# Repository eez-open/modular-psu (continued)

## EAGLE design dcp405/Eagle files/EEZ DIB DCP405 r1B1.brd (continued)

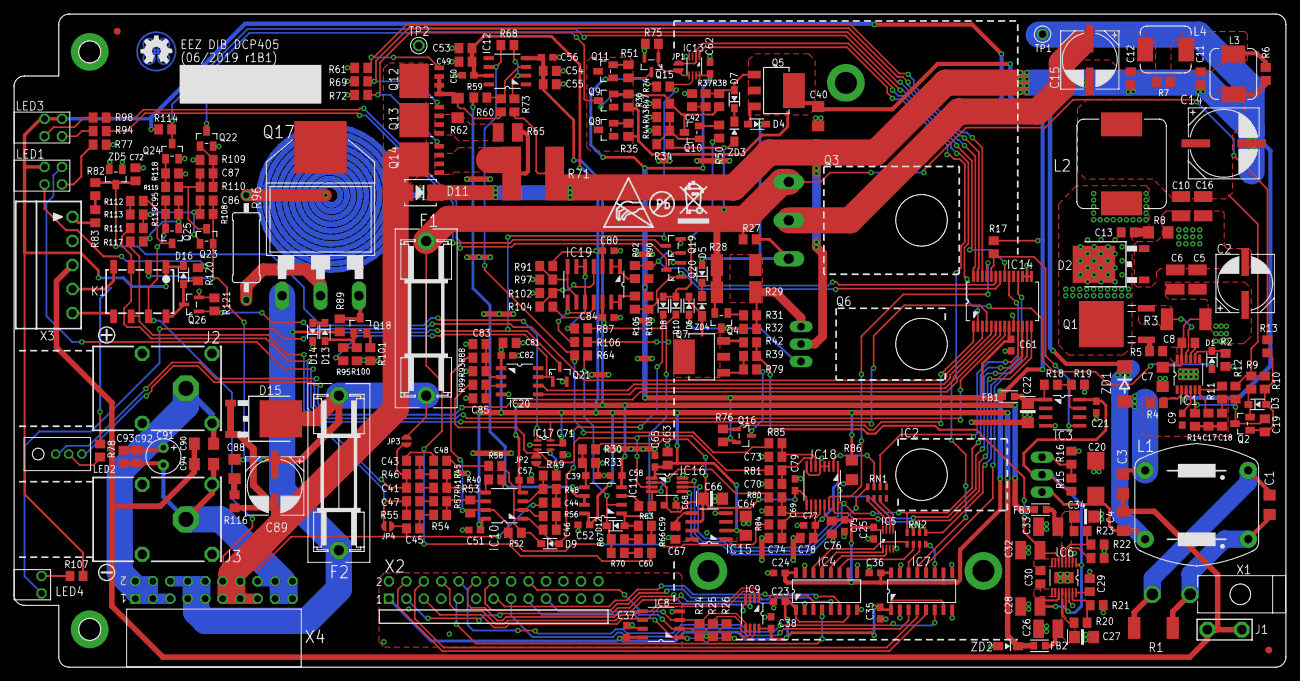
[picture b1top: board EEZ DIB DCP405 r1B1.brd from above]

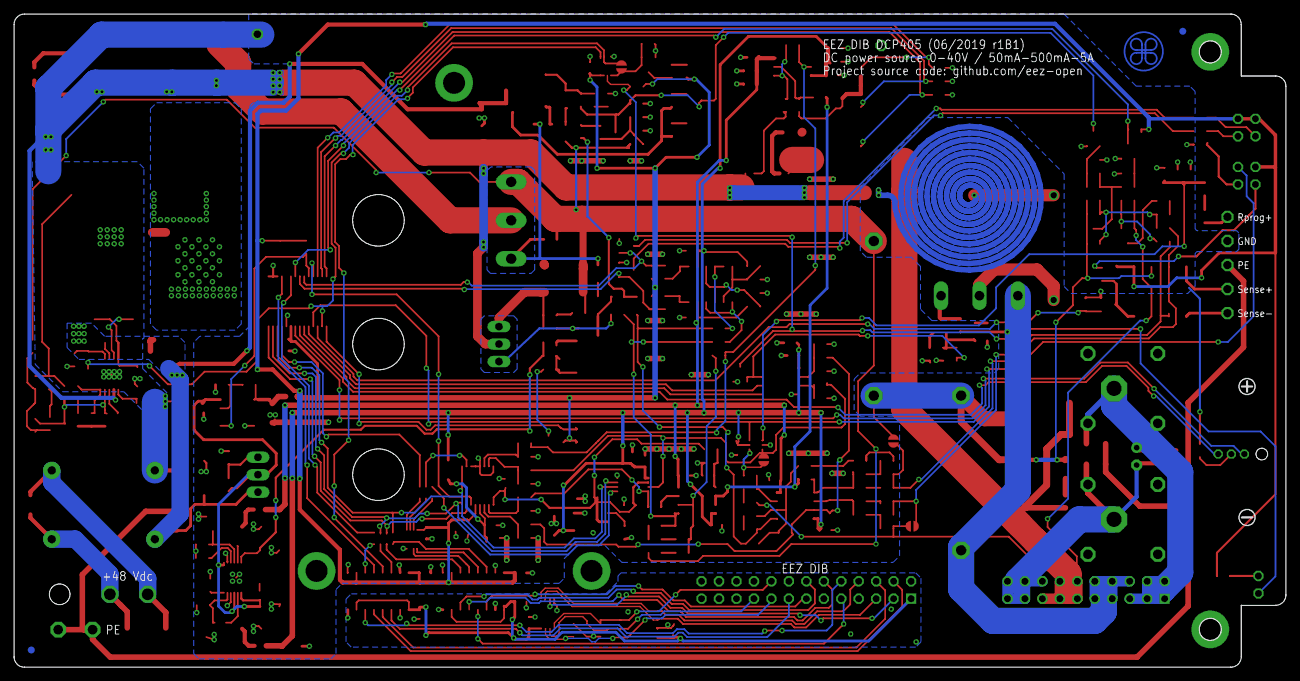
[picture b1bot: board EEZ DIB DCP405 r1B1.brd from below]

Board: 2 copper layers, 185.0 x 95.0 mm, 323 parts (3 on the bottom side), 200 nets.

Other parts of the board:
EEZ_SIGNATURE: SIGNATURESMALL; SIGNATURE_5MM
U$1: RECYCLE_BIN1/8
U$6: ESD_SYMBOL
U$7: PB_SMALL

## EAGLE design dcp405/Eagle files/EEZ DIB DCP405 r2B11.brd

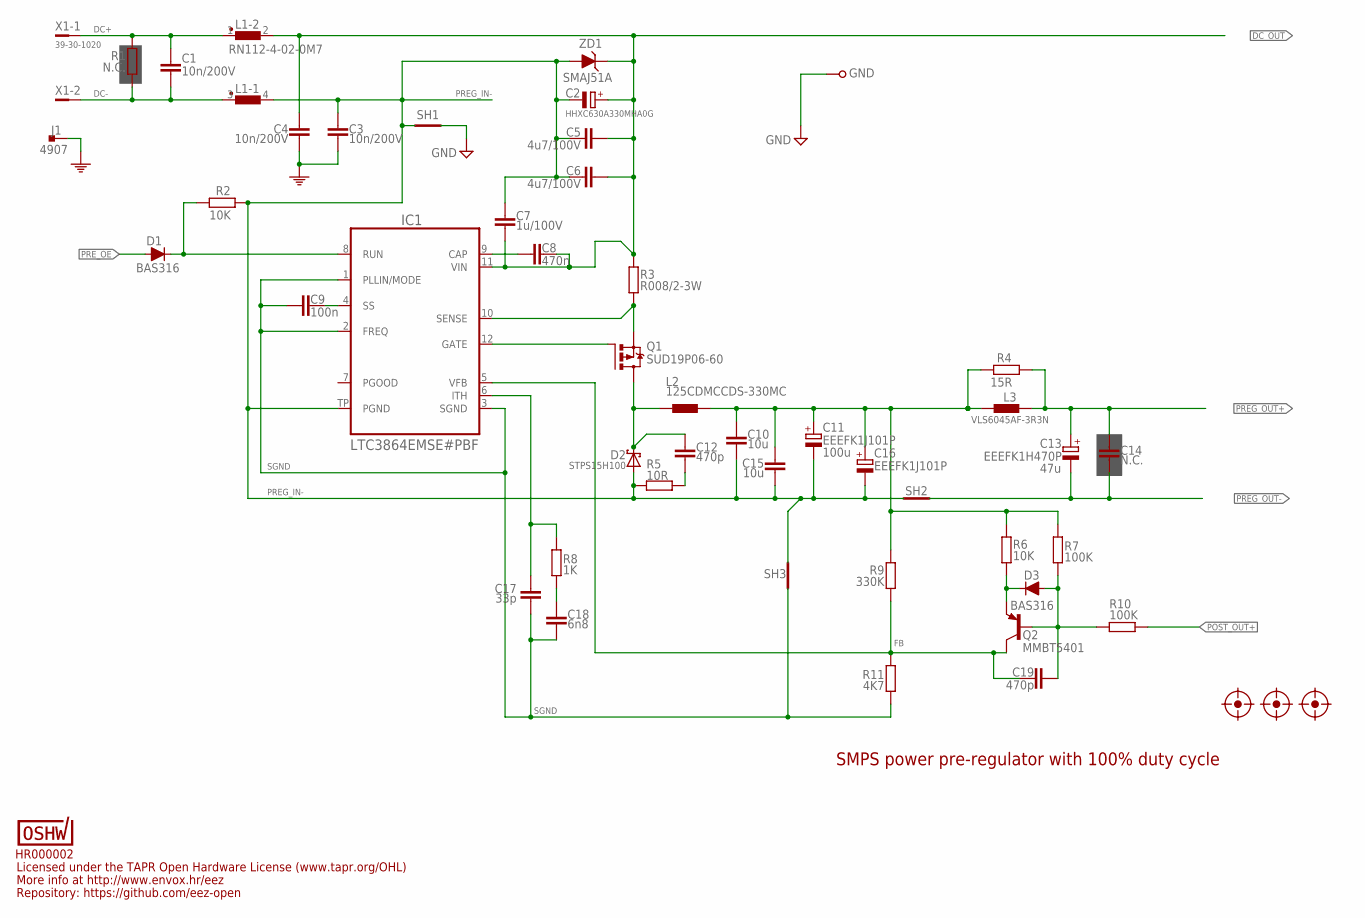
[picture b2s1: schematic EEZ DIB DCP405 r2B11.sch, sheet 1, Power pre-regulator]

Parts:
C1, C3, C4: 10n/200V; C1206
C2: HHXC630A330MHA0G; CAPAE830X1050N
C5, C6: 4u7/100V; C1210
C7: 1u/100V; C1206
C8: 470n; C0805
C9: 100n; C0603
C10, C15: 10u; C1210
C11, C16: EEEFK1J101P; CAPAE1030X1050N
C12, C19: 470p; C0805
C13: EEEFK1H470P; CAPAE830X1050N
C14: N.C.; C0805
C17: 33p; C0805
C18: 6n8; C0805
D1, D3: BAS316; SOD323-R
D2: STPS15H100; TO252-L
FM1, FM2, FM3: FIDUCIAL_2; FIDUCIAL_DUAL
GND: PCB_TEST_TABSHIELD; PCB_SHIELD_TAB
IC1: LTC3864EMSE#PBF; LTC_05-08-1666
J1: 4907; PCB_TAB-4907
L1: RN112-4-02-0M7; RN112
L2: 125CDMCCDS-330MC; 125CDMCC/DS
L3: VLS6045AF-3R3N; COILCRAFT_HPI0630
OSHWA: HR000002; CERT-SMALL-SILK
Q1: SUD19P06-60; TO229P990X239-3N
Q2: MMBT5401; SOT23-BEC
R1: N.C.; R2512
R2, R6: 10K; R0805
R3: R008/2-3W; R2512
R4: 15R; R2010
R5: 10R; R1206
R7, R10: 100K; R0805
R8: 1K; R0805
R9: 330K; R0805
R11: 4K7; R0805
SH1: SHORTNOHOLE; SHORT_NOHOLE
SH2: Pgnd to Pout- short; SHORT_NOHOLE
SH3: Sgnd to Pgnd short; SHORT_NOHOLE
X1: 39-30-1020; MINIFIT_39301020
ZD1: SMAJ51A; DO214AA

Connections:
DC+: C1.2, L1.1, R1.2, X1.1
DC-: C1.1, L1.3 (1), R1.1, X1.2
DC_OUT: C2.+, C4.2, C5.1, C6.1, C7.1, C8.2, IC1.11 (VIN), L1.2, R3.1, ZD1.C; also elsewhere on the board
FB: C19.1, IC1.5 (VFB), Q2.C, R9.2, R11.1
GND: GND.1, SH1.2 (GND_B); also elsewhere on the board
L_OUT: C10.1, C11.+, C15.1, C16.+, L2.2, L3.1, R4.1, R6.1, R7.1, R9.1
unnamed: D3.C, Q2.E, R6.2
unnamed: C18.1, R8.1
unnamed: D1.C, IC1.8 (RUN), R2.2
unnamed: C17.1, IC1.6 (ITH), R8.2
unnamed: C8.1, IC1.9 (CAP)
unnamed: C9.2, IC1.4 (SS)
unnamed: IC1.12 (GATE), Q1.1 (G)
unnamed: C12.2, R5.2
unnamed: C19.2, D3.A, Q2.B, R7.2, R10.1
PE: C3.2, C4.1, J1.1, J1.2; also elsewhere on the board
POST_OUT+: R10.2; also elsewhere on the board
PREG_IN-: C2.-, C3.1, C5.2, C6.2, C7.2, C10.2, C11.-, C15.2, C16.-, D2.1 (A), D2.2 (A), IC1.TP (PGND), L1.4 (2), R2.1, R5.1, SH1.1 (GND_A), SH2.2 (GND_B), SH3.2 (GND_B), ZD1.A
PREG_OUT+: C13.+, C14.1, L3.2, R4.2; also elsewhere on the board
PREG_OUT-: C13.-, C14.2, SH2.1 (GND_A); also elsewhere on the board
PRE_OE: D1.A; also elsewhere on the board
SENSE: IC1.10 (SENSE), Q1.3 (S), R3.2
SGND: C9.1, C17.2, C18.2, IC1.1 (PLLIN/MODE), IC1.2 (FREQ), IC1.3 (SGND), R11.2, SH3.1 (GND_A)
SW: C12.1, D2.3 (C), L2.1, Q1.2 (D)

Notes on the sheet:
47u
Licensed under the TAPR Open Hardware License (www.tapr.org/OHL)
Repository: https://github.com/eez-open
More info at http://www.envox.hr/eez
SMPS power pre-regulator with 100% duty cycle
100u

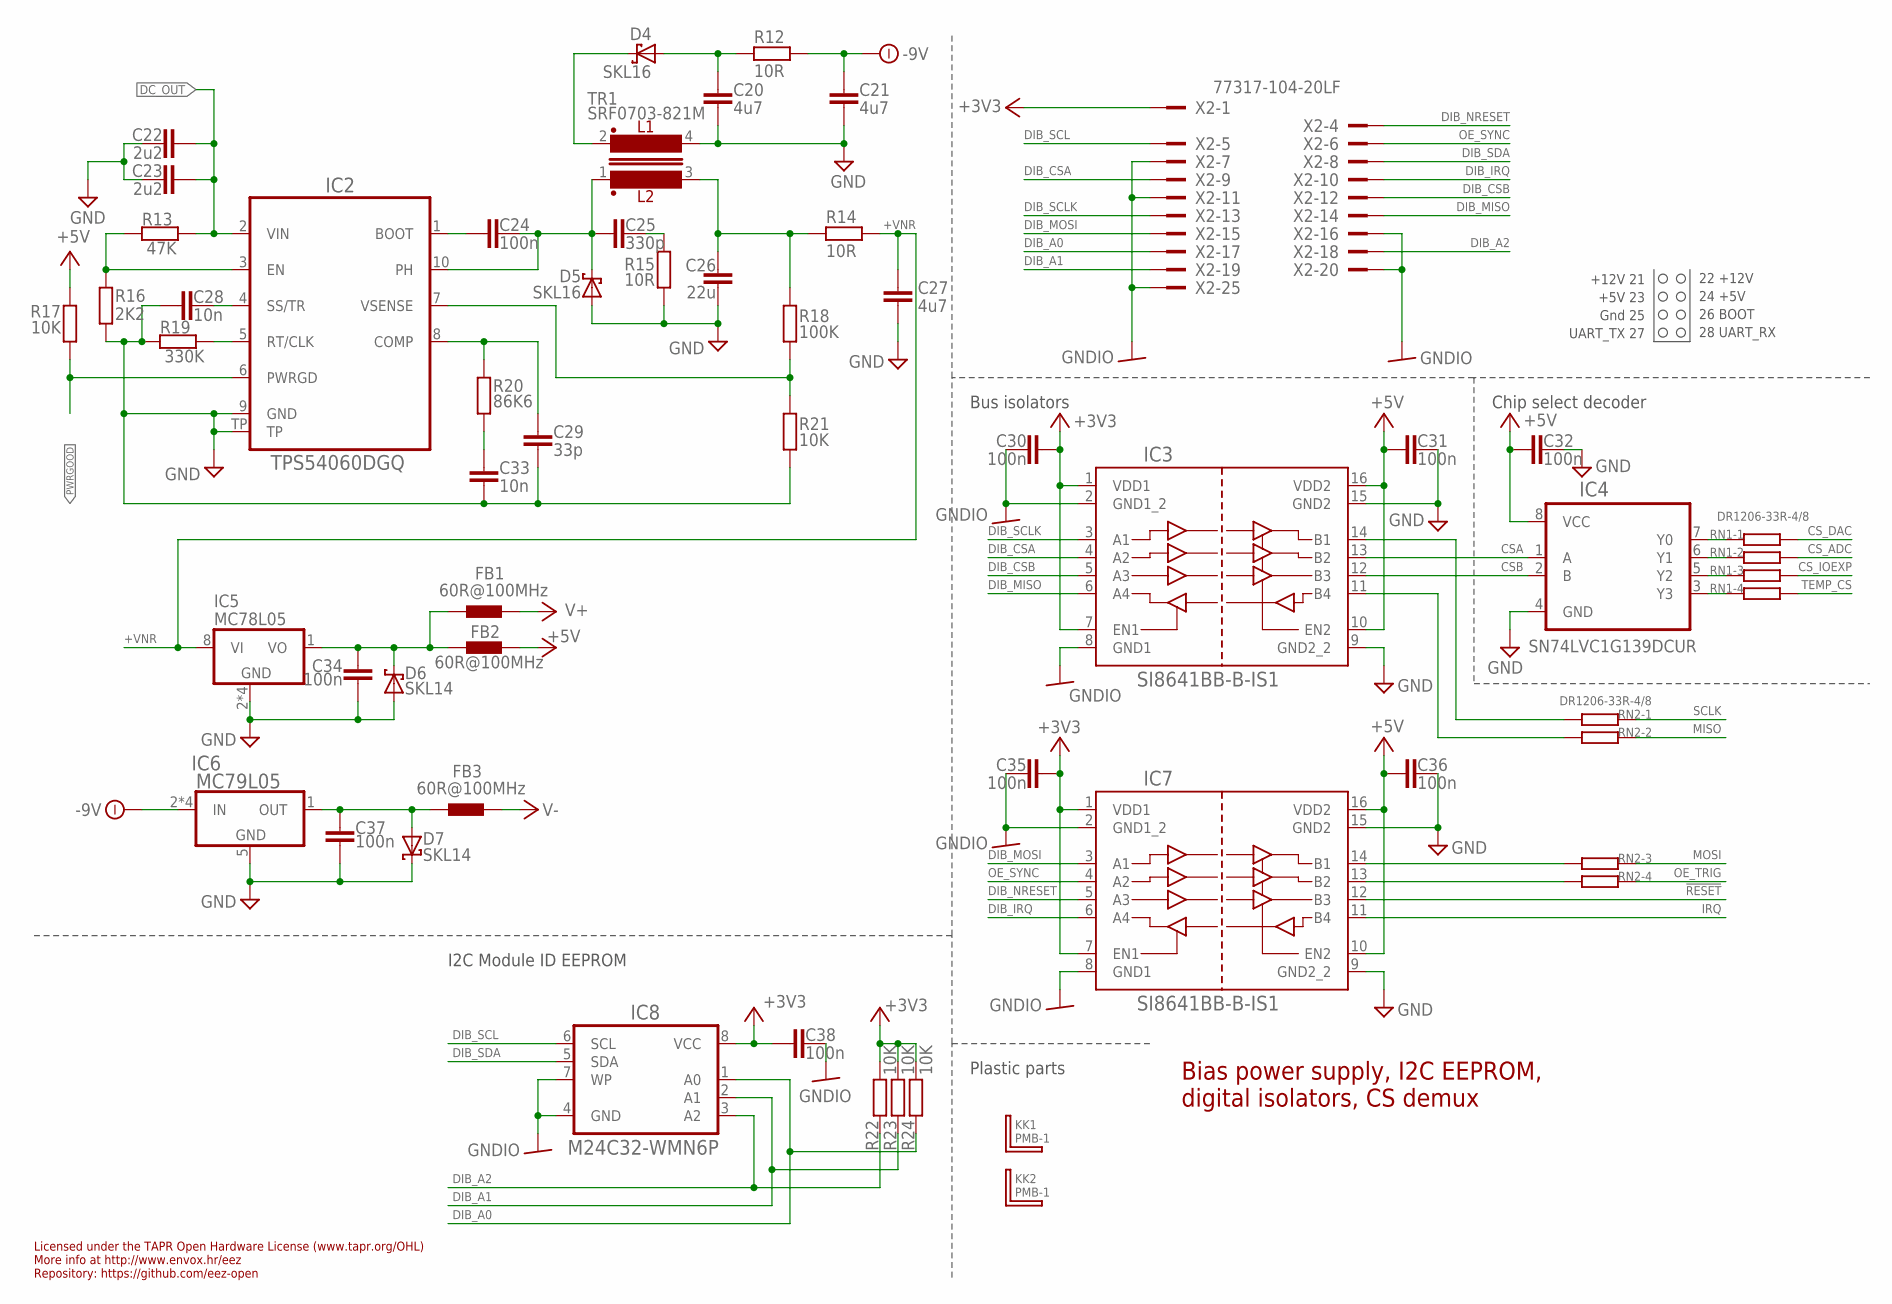
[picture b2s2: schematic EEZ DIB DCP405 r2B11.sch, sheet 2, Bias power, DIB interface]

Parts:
C20, C21, C27: 4u7; C1206
C22, C23: 2u2; C1206
C24, C30, C31, C32, C34, C35, C36, C37, C38: 100n; C0603
C25: 330p; C0805
C26: 22u; C1210
C28, C33: 10n; C0805
C29: 33p; C0805
D4, D5: SKL16; SOD123
D6, D7: SKL14; SOD123
FB1, FB2, FB3: 60R@100MHz; BEAD0603
IC2: TPS54060DGQ; SOP50P490X110-11N
IC3, IC7: SI8641BB-B-IS1; SOIC-16
IC4: SN74LVC1G139DCUR; DCU8
IC5: MC78L05; SOIC127P600X173-8N
IC6: MC79L05; SOIC127P600X173-8N
IC8: M24C32-WMN6P; SOIC127P600X173-8N
KK1, KK2: PMB-1; PCB-MB
R12, R14, R15: 10R; R1206
R13: 47K; R0805
R16: 2K2; R0805
R17, R21, R22, R23, R24: 10K; R0805
R18: 100K; R0805
R19: 330K; R0805
R20: 86K6; R0805
RN1, RN2: DR1206-33R-4/8; CAY16
TR1: SRF0703-821M; SRF0703
X2: 77317-104-20LF; 77317-104-28LF

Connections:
!RESET: IC7.12 (B3); also elsewhere on the board
+3V3: C30.1, C35.1, C38.2, IC3.1 (VDD1), IC3.7 (EN1), IC7.1 (VDD1), IC7.7 (EN1), IC8.8 (VCC), R22.1, R23.1, R24.1, X2.1
+5V: C31.2, C32.1, C36.2, FB2.P$2 (2), IC3.10 (EN2), IC3.16 (VDD2), IC4.8 (VCC), IC7.10 (EN2), IC7.16 (VDD2), R17.1; also elsewhere on the board
+5VOUT: C34.1, D6.C, FB1.P$1 (1), FB2.P$1 (1), IC5.1 (VO)
+VNR: C27.1, IC5.8 (VI), R14.1
-9V: C21.1, IC6.2 (IN), IC6.3 (IN), IC6.6 (IN), IC6.7 (IN), R12.1; also elsewhere on the board
CSA: IC3.13 (B2), IC4.1 (A)
CSB: IC3.12 (B3), IC4.2 (B)
CS_ADC: RN1.7 (2); also elsewhere on the board
CS_DAC: RN1.8 (2); also elsewhere on the board
CS_IOEXP: RN1.6 (2); also elsewhere on the board
DC_OUT: C22.1, C23.1, IC2.2 (VIN), R13.2; also elsewhere on the board
DIB_A0: IC8.1 (A0), R24.2, X2.17
DIB_A1: IC8.2 (A1), R23.2, X2.19
DIB_A2: IC8.3 (A2), R22.2, X2.18
DIB_CSA: IC3.4 (A2), X2.9
DIB_CSB: IC3.5 (A3), X2.12
DIB_IRQ: IC7.6 (A4), X2.10
DIB_MISO: IC3.6 (A4), X2.14
DIB_MOSI: IC7.3 (A1), X2.15
DIB_NRESET: IC7.5 (A3), X2.4
DIB_SCL: IC8.6 (SCL), X2.5
DIB_SCLK: IC3.3 (A1), X2.13
DIB_SDA: IC8.5 (SDA), X2.8
GND: C20.2, C21.2, C22.2, C23.2, C26.2, C27.2, C28.2, C29.1, C31.1, C32.2, C33.1, C34.2, C36.1, C37.1, D5.A, D6.A, D7.C, IC2.9 (GND), IC2.TP, IC3.9 (GND2_2), IC3.15 (GND2), IC4.4 (GND), IC5.2 (GND), IC5.3 (GND), IC5.6 (GND), IC5.7 (GND), IC6.5 (GND), IC7.9 (GND2_2), IC7.15 (GND2), R15.1, R16.1, R19.1, R21.1, TR1.4; also elsewhere on the board
GNDIO: C30.2, C35.2, C38.1, IC3.2 (GND1_2), IC3.8 (GND1), IC7.2 (GND1_2), IC7.8 (GND1), IC8.4 (GND), IC8.7 (WP), X2.7, X2.11, X2.16, X2.20, X2.25
IRQ: IC7.11 (B4); also elsewhere on the board
MISO: RN2.7 (2); also elsewhere on the board
MOSI: RN2.6 (2); also elsewhere on the board
unnamed: IC7.13 (B2), RN2.4 (1)
unnamed: IC4.5 (Y2), RN1.3 (1)
unnamed: IC4.7 (Y0), RN1.1
unnamed: IC3.11 (B4), RN2.2 (1)
unnamed: IC4.6 (Y1), RN1.2 (1)
unnamed: C25.2, R15.2
unnamed: C37.2, D7.A, FB3.P$1 (1), IC6.1 (OUT)
unnamed: IC2.3 (EN), R13.1, R16.2
unnamed: C28.1, IC2.4 (SS/TR)
unnamed: IC2.5 (RT/CLK), R19.2
unnamed: C29.2, IC2.8 (COMP), R20.2
unnamed: C33.2, R20.1
unnamed: IC4.3 (Y3), RN1.4 (1)
unnamed: C24.2, IC2.1 (BOOT)
unnamed: IC7.14 (B1), RN2.3 (1)
unnamed: IC2.7 (VSENSE), R18.1, R21.2
unnamed: IC3.14 (B1), RN2.1
unnamed: C20.1, D4.A, R12.2
OE_SYNC: IC7.4 (A2), X2.6
OE_TRIG: RN2.5 (2); also elsewhere on the board
PH: C24.1, C25.1, D5.C, IC2.10 (PH), TR1.1
PWRGOOD: IC2.6 (PWRGD), R17.2; also elsewhere on the board
SCLK: RN2.8 (2); also elsewhere on the board
TEMP_CS: RN1.5 (2); also elsewhere on the board
V+: FB1.P$2 (2); also elsewhere on the board
V-: FB3.P$2 (2); also elsewhere on the board
VOUT+: C26.1, R14.2, R18.2, TR1.3
VOUT-: D4.C, TR1.2

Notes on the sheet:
Licensed under the TAPR Open Hardware License (www.tapr.org/OHL)
Repository: https://github.com/eez-open
More info at http://www.envox.hr/eez
I2C Module ID EEPROM
Bus isolators
Bias power supply, I2C EEPROM, digital isolators, CS demux
Plastic parts
Chip select decoder
22 +12V
24 +5V
+5V 23
Gnd 25
+12V 21
26 BOOT
UART_TX 27
28 UART_RX

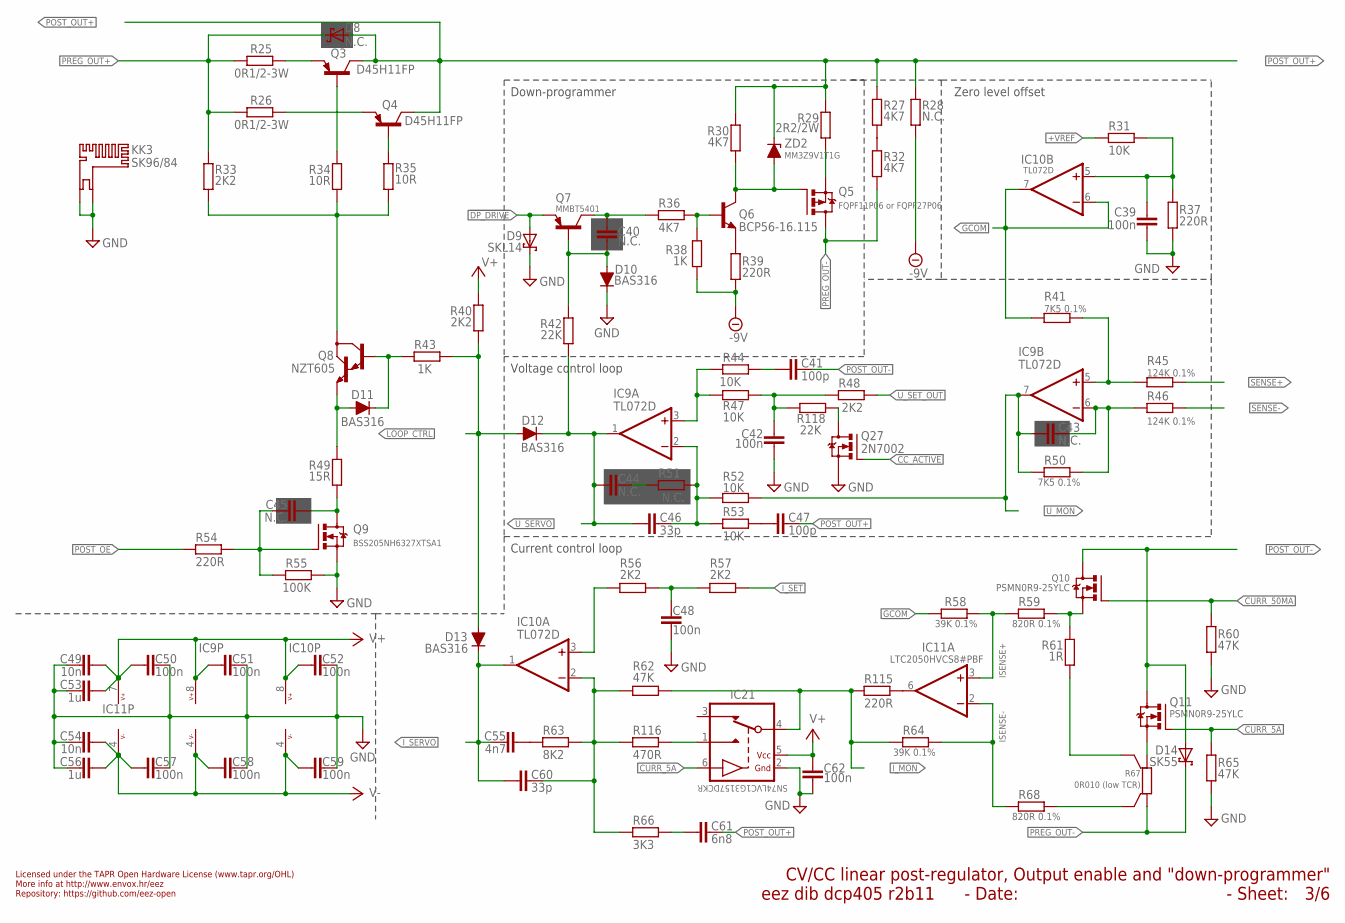
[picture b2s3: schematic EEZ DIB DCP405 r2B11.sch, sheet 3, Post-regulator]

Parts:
C39, C42, C48, C50, C51, C52, C57, C58, C59, C62: 100n; C0603
C40, C43, C44, C45: N.C.; C0805
C41, C47: 100p; C0805
C46, C60: 33p; C0805
C49, C54: 10n; C0805
C53, C56: 1u; C0805
C55: 4n7; C0805
C61: 6n8; C0805
D8: N.C.; SOD123
D9: SKL14; SOD123
D10, D11, D12, D13: BAS316; SOD323-R
D14: SK55; SMB
IC9, IC10: TL072D; SOIC127P600X173-8N
IC11: LTC2050HVCS8#PBF; SOIC127P600X173-8N
IC21: SN74LVC1G3157DCKR; SOT65P210X110-6N
KK3: SK96/84
Q3, Q4: D45H11FP; TO220FP-V
Q5: FQPF11P06 or FQPF27P06; TO220FP-V
Q6: BCP56-16.115; SOT230P700X180-4N
Q7: MMBT5401; SOT23-BEC
Q8: NZT605; SOT230P700X180-4N
Q9: BSS205NH6327XTSA1; SOT103P240X110-3N; MPN 2N7002-7-F
Q10, Q11: PSMN0R9-25YLC; SOT669
Q27: 2N7002; SOT103P240X110-3N
R25, R26: 0R1/2-3W; R2512
R27, R30, R32, R36: 4K7; R0805
R28, R51: N.C.; R0805
R29: 2R2/2W; R2512
R31, R44, R47, R52, R53: 10K; R0805
R33, R40, R48, R56, R57: 2K2; R0805
R34, R35: 10R; R1206
R37, R39, R54, R115: 220R; R0805
R38, R43: 1K; R0805
R41, R50: 7K5 0.1%; R0805
R42, R118: 22K; R0805
R45, R46: 124K 0.1%; R0805
R49: 15R; R2010
R55: 100K; R0805
R58, R64: 39K 0.1%; R0805
R59, R68: 820R 0.1%; R0805
R60, R62, R65: 47K; R0805
R61: 1R; R1206
R63: 8K2; R0805
R66: 3K3; R0805
R67: 0R010 (low TCR); R_2512-4WIRE
R116: 470R; R0805
ZD2: MM3Z9V1T1G; SOD323-R

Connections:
5A_S: Q11.1 (S), Q11.2 (S), Q11.3 (S), R67.2
50MA_S: Q10.1 (S), Q10.2 (S), Q10.3 (S), R59.1, R61.1
!DP_DRIVE: D9.A, Q7.E; also elsewhere on the board
+VREF: R31.1; also elsewhere on the board
-9V: R28.1, R38.2, R39.2; also elsewhere on the board
CC_ACTIVE: Q27.1 (G); also elsewhere on the board
CURR_5A: IC21.6 (CTRL), Q11.4 (G), R65.2; also elsewhere on the board
CURR_50MA: Q10.4 (G), R60.2; also elsewhere on the board
DARL_C: Q8.2 (C), Q8.4 (C), R33.1, R34.1, R35.1
DP_S: Q5.3 (S), R29.1
GCOM: IC10.6 (-IN), IC10.7 (OUT), R41.1, R58.1
GND: C39.2, C42.2, C48.2, C49.1, C50.2, C51.1, C52.1, C53.1, C54.1, C56.1, C57.2, C58.1, C59.1, C62.2, D9.C, D10.C, IC21.2 (GND), KK3.1, KK3.2, Q9.2 (S), Q27.2 (S), R37.2, R55.1, R60.1, R65.1; also elsewhere on the board
ISENSE+: IC11.3 (+IN), R58.2, R59.2
ISENSE-: IC11.2 (-IN), R64.1, R68.2
I_MON: IC21.4 (COM), R62.1, R64.2, R115.1; also elsewhere on the board
I_SERVO: C55.2, C60.2, D13.C, IC10.1 (OUT); also elsewhere on the board
I_SET: R57.1; also elsewhere on the board
LOOP_CTRL: D12.A, D13.A, R40.1, R43.1; also elsewhere on the board
unnamed: C48.1, R56.1, R57.2
unnamed: R61.2, R67.2S
unnamed: C44.1, R51.2
unnamed: C45.2, Q9.3 (D), R49.1
unnamed: C55.1, R63.1
unnamed: Q6.1 (B), R36.1, R38.1
unnamed: Q4.1 (B), R35.2
unnamed: Q3.1 (B), R34.2
unnamed: C40.2, Q7.C, R36.2
unnamed: D11.C, Q8.1 (B), R43.2
unnamed: D11.A, Q8.3 (E), R49.2
unnamed: R27.1, R32.2
unnamed: C45.1, Q9.1 (G), R54.1, R55.2
unnamed: IC11.6 (OUT), R115.2
unnamed: C40.1, D10.A, Q7.B, R42.2
unnamed: IC21.1 (NO), R116.1
unnamed: Q27.3 (D), R118.1
unnamed: IC10.3 (+IN), R56.2
unnamed: IC9.3 (+IN), R44.2, R47.2
unnamed: C46.1, IC9.2 (-IN), R51.1, R52.2, R53.2
unnamed: C61.2, R66.1
unnamed: C60.1, IC10.2 (-IN), R62.2, R63.2, R66.2, R116.2
unnamed: C41.2, R44.1
unnamed: C47.2, R53.1
unnamed: Q6.3 (E), R39.1
unnamed: C39.1, IC10.5 (+IN), R31.2, R37.1
unnamed: IC9.5 (+IN), R41.2, R45.1
unnamed: C43.1, IC9.6 (-IN), R46.1, R50.2
unnamed: R67.1S, R68.1
PASS_E1: Q3.3 (E), R25.2
PASS_E2: Q4.3 (E), R26.2
POST_OE: R54.2; also elsewhere on the board
POST_OUT+: C47.1, C61.1, D8.A, Q3.2 (C), Q4.2 (C), R27.2, R28.2, R29.2, R30.1, ZD2.C; also elsewhere on the board
POST_OUT-: C41.1, D14.A, Q10.MB (D), Q11.MB (D); also elsewhere on the board
PREG_OUT+: D8.C, R25.1, R26.1, R33.2; also elsewhere on the board
PREG_OUT-: D14.C, Q5.2 (D), R32.1, R67.1; also elsewhere on the board
Q6C: Q5.1 (G), Q6.2 (C), Q6.4 (C), R30.2, ZD2.A
SENSE+: R45.2; also elsewhere on the board
SENSE-: R46.2; also elsewhere on the board
U_MON: C43.2, IC9.7 (OUT), R50.1, R52.1; also elsewhere on the board
U_SERVO: C44.2, C46.2, D12.C, IC9.1 (OUT), R42.1; also elsewhere on the board
U_SET_OUT: R48.1; also elsewhere on the board
U_SET_OVP: C42.1, R47.1, R48.2, R118.2
V+: C49.2, C50.1, C51.2, C52.2, C53.2, C62.1, IC9.8 (V+), IC10.8 (V+), IC11.7 (V+), IC21.5 (VDD), R40.2; also elsewhere on the board
V-: C54.2, C56.2, C57.1, C58.2, C59.2, IC9.4 (V-), IC10.4 (V-), IC11.4 (V-); also elsewhere on the board

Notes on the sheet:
Voltage control loop
Down-programmer
Licensed under the TAPR Open Hardware License (www.tapr.org/OHL)
Repository: https://github.com/eez-open
More info at http://www.envox.hr/eez
Zero level offset
CV/CC linear post-regulator, Output enable and "down-programmer"
- Sheet:
- Date:
Current control loop

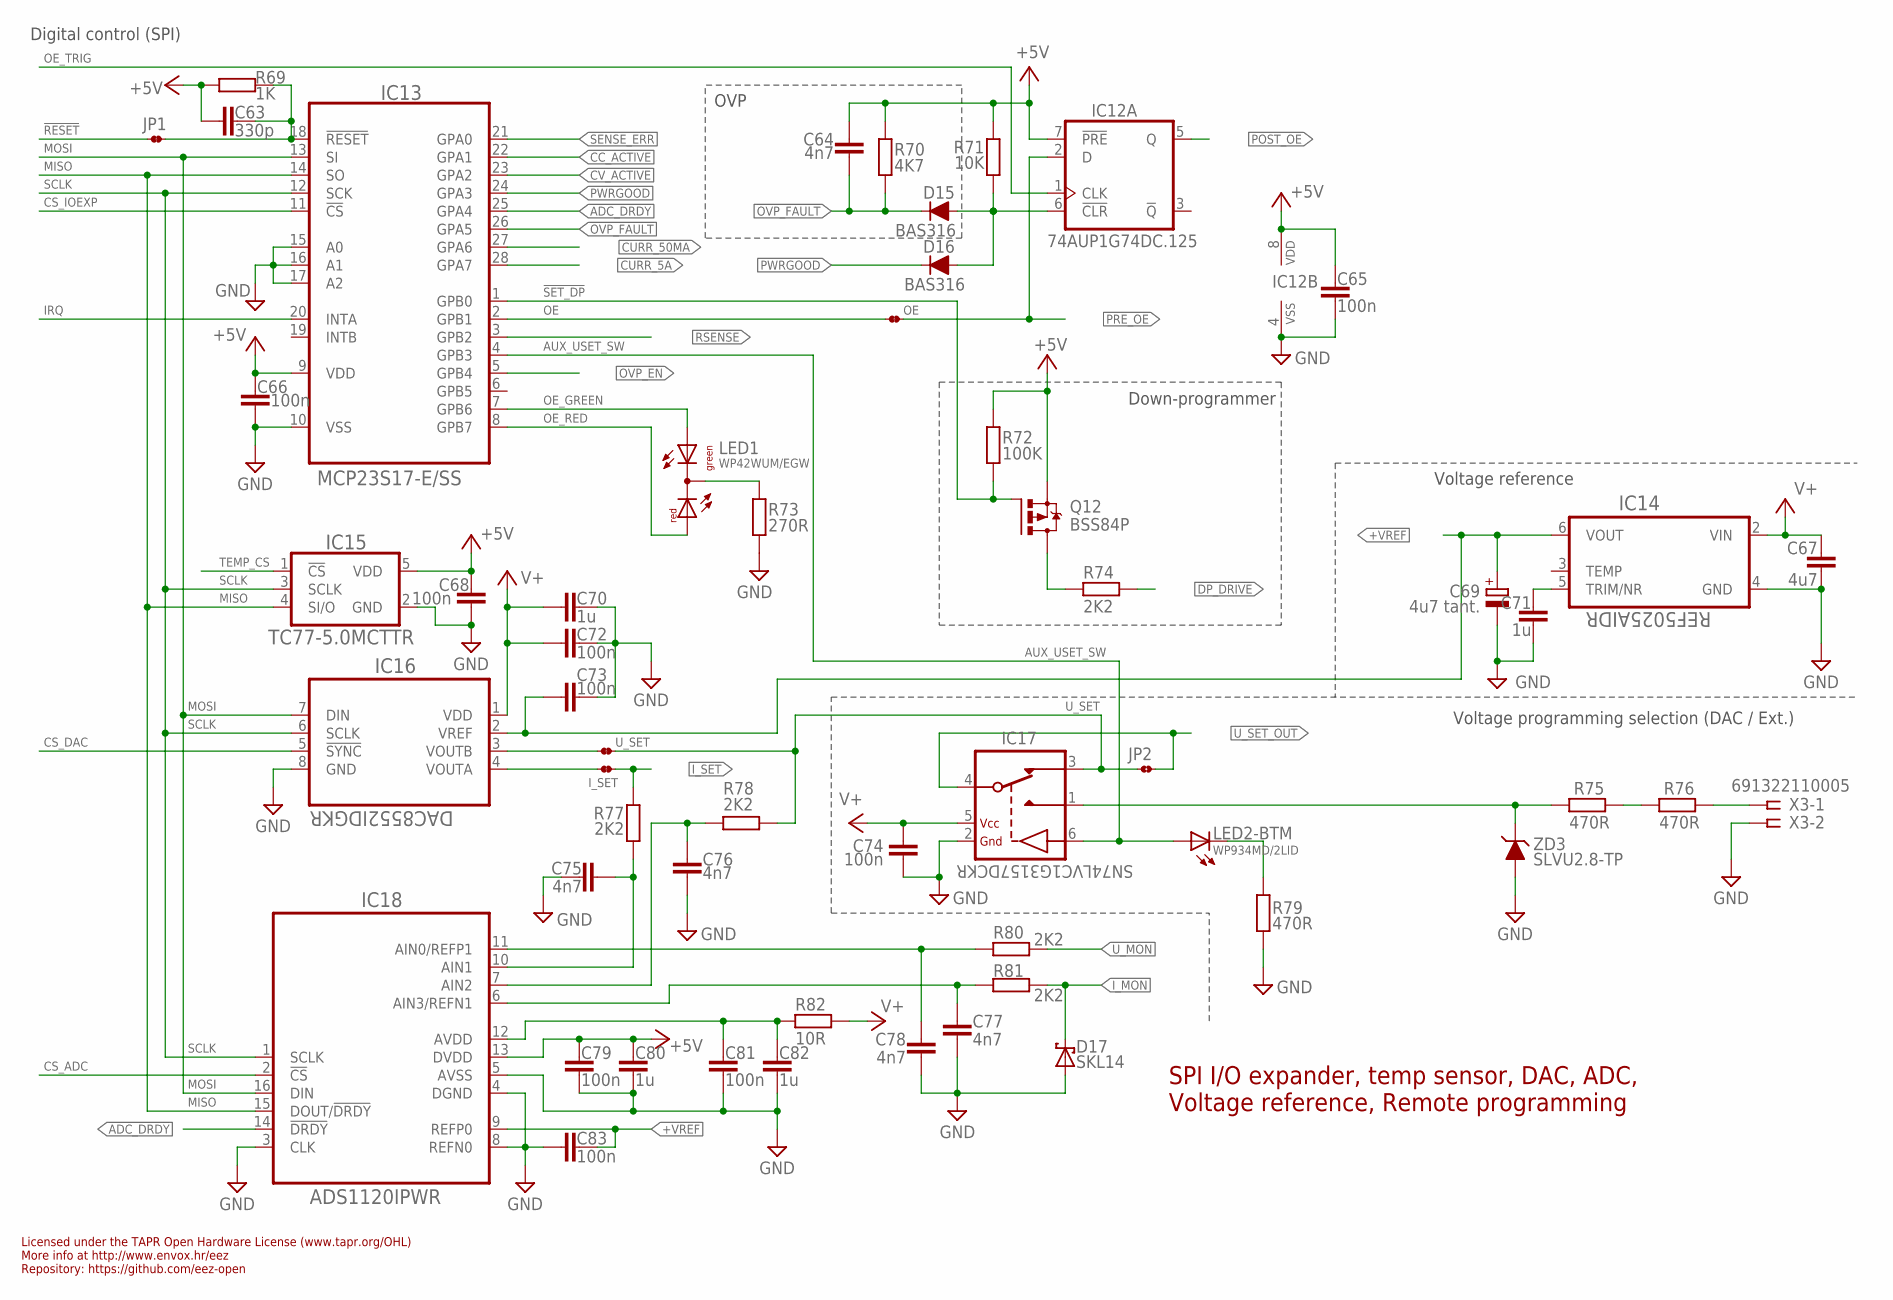
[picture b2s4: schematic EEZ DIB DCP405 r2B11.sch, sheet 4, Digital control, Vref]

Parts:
C63: 330p; C0805
C64, C75, C76, C77, C78: 4n7; C0805
C65, C66, C68, C72, C73, C74, C79, C81, C83: 100n; C0603
C67: 4u7; C1206
C69: 4u7 tant.; EC1206
C70, C71, C80, C82: 1u; C0805
D15, D16: BAS316; SOD323-R
D17: SKL14; SOD123
IC12: 74AUP1G74DC.125; DCU8
IC13: MCP23S17-E/SS; SOP65P780X200-28N
IC14: REF5025AIDR; SOIC127P600X175-8N
IC15: TC77-5.0MCTTR; SOT23-5
IC16: DAC8552IDGKR; DGK8-M
IC17: SN74LVC1G3157DCKR; SOT65P210X110-6N
IC18: ADS1120IPWR; PW(R-PDSO-G16)
I_SET: JP2-NOCUT
JP1: JP2-NOCUT
JP2: JP2-CUT-0805; R_0805
LED1: WP42WUM/EGW; L-42WUM-1EGWT
LED2: WP934MD/2LID; WP934MD
OE: JP2-NOCUT
Q12: BSS84P; SOT95P237X112-3N
R69: 1K; R0805
R70: 4K7; R0805
R71: 10K; R0805
R72: 100K; R0805
R73: 270R; R0805
R74, R77, R78, R80, R81: 2K2; R0805
R75, R76, R79: 470R; R0805
R82: 10R; R1206
U_SET: JP2-NOCUT
X3: 691322110005; MC1,5/5-G-3,5
ZD3: SLVU2.8-TP; SOT23

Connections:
!ADC_DRDY: IC13.25 (GPA4), IC18.14 (!DRDY)
!DP_DRIVE: R74.1; also elsewhere on the board
!IOEXP_RST: C63.1, IC13.18 (!RESET), JP1.2, R69.2
!OVP_FAULT: C64.1, D15.C, IC13.26 (GPA5), R70.2; also elsewhere on the board
!RESET: JP1.1; also elsewhere on the board
!SET_DP: IC13.1 (GPB0), Q12.1 (G), R72.2
+5V: C63.2, C64.2, C65.2, C66.1, C68.1, C79.2, C80.2, IC12.7 (!PRE), IC12.8 (VDD), IC13.9 (VDD), IC15.5 (VDD), IC18.13 (DVDD), Q12.2 (S), R69.1, R70.1, R71.1, R72.1; also elsewhere on the board
+VREF: C69.+, C73.2, C83.2, IC14.6 (VOUT), IC16.2 (VREF), IC18.9 (REFP0); also elsewhere on the board
AUX_IN: IC17.1 (NO), R75.1, ZD3.3 (C)
AUX_USET_SW: IC13.4 (GPB3), IC17.6 (CTRL), LED2.BA (A)
CC_ACTIVE: IC13.22 (GPA1); also elsewhere on the board
CS_ADC: IC18.2 (!CS); also elsewhere on the board
CS_DAC: IC16.5 (!SYNC); also elsewhere on the board
CS_IOEXP: IC13.11 (!CS); also elsewhere on the board
CURR_5A: IC13.28 (GPA7); also elsewhere on the board
CURR_50MA: IC13.27 (GPA6); also elsewhere on the board
CV_ACTIVE: IC13.23 (GPA2); also elsewhere on the board
GND: C65.1, C66.2, C67.2, C68.2, C69.-, C70.2, C71.2, C72.1, C73.1, C74.2, C75.1, C76.1, C77.2, C78.1, C79.1, C80.1, C81.1, C82.1, C83.1, D17.A, IC12.4 (VSS), IC13.10 (VSS), IC13.15 (A0), IC13.16 (A1), IC13.17 (A2), IC14.4 (GND), IC15.2 (GND), IC16.8 (GND), IC17.2 (GND), IC18.3 (CLK), IC18.4 (DGND), IC18.5 (AVSS), IC18.8 (REFN0), R73.2, R79.1, X3.2, ZD3.1 (A), ZD3.2 (A); also elsewhere on the board
IRQ: IC13.20 (INTA); also elsewhere on the board
I_MON: D17.C, R81.1; also elsewhere on the board
I_SET: I_SET.2, R77.1; also elsewhere on the board
MISO: IC13.14 (SO), IC15.4 (SI/O), IC18.15 (DOUT/!DRDY); also elsewhere on the board
MOSI: IC13.13 (SI), IC16.7 (DIN), IC18.16 (DIN); also elsewhere on the board
unnamed: LED1.CC (C), R73.1
unnamed: IC16.4 (VOUTA), I_SET.1
unnamed: R75.2, R76.1
unnamed: R76.2, X3.1
unnamed: IC16.3 (VOUTB), U_SET.1
unnamed: Q12.3 (D), R74.2
unnamed: D15.A, D16.A, IC12.6 (!CLR), R71.2
unnamed: C81.2, C82.2, IC18.12 (AVDD), R82.2
unnamed: C71.1, IC14.5 (TRIM/NR)
unnamed: C75.2, IC18.10 (AIN1), R77.2
unnamed: C78.2, IC18.11 (AIN0/REFP1), R80.2
unnamed: C76.2, IC18.7 (AIN2), R78.2
unnamed: C77.1, IC18.6 (AIN3/REFN1), R81.2
unnamed: LED2.BC (C), R79.2
OE: IC13.2 (GPB1), OE.1
OE_GREEN: IC13.7 (GPB6), LED1.GREEN (AG)
OE_RED: IC13.8 (GPB7), LED1.RED (AR)
OE_TRIG: IC12.1 (CLK); also elsewhere on the board
OVP_EN: IC13.5 (GPB4); also elsewhere on the board
POST_OE: IC12.5 (Q); also elsewhere on the board
PRE_OE: IC12.2 (D), OE.2; also elsewhere on the board
PWRGOOD: D16.C, IC13.24 (GPA3); also elsewhere on the board
RSENSE: IC13.3 (GPB2); also elsewhere on the board
SCLK: IC13.12 (SCK), IC15.3 (SCLK), IC16.6 (SCLK), IC18.1 (SCLK); also elsewhere on the board
SENSE_ERR: IC13.21 (GPA0); also elsewhere on the board
TEMP_CS: IC15.1 (!CS); also elsewhere on the board
U_MON: R80.1; also elsewhere on the board
U_SET: IC17.3 (NC), JP2.1, R78.1, U_SET.2
U_SET_OUT: IC17.4 (COM), JP2.2; also elsewhere on the board
V+: C67.1, C70.1, C72.2, C74.1, IC14.2 (VIN), IC16.1 (VDD), IC17.5 (VDD), R82.1; also elsewhere on the board

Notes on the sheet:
Digital control (SPI)
Voltage reference
Licensed under the TAPR Open Hardware License (www.tapr.org/OHL)
Repository: https://github.com/eez-open
More info at http://www.envox.hr/eez
SPI I/O expander, temp sensor, DAC, ADC, Voltage reference, Remote programming
Voltage programming selection (DAC / Ext.)
OVP
Down-programmer

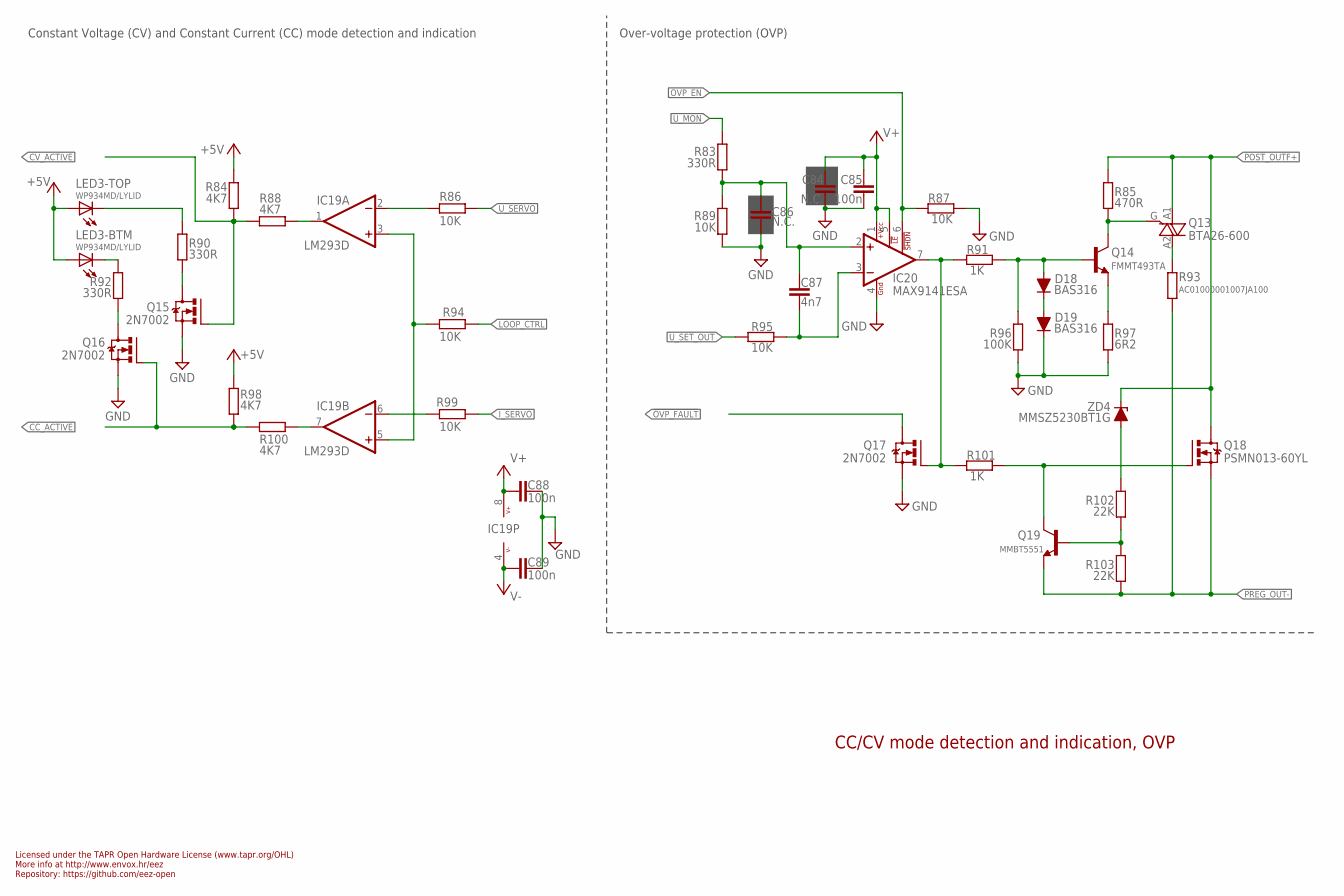
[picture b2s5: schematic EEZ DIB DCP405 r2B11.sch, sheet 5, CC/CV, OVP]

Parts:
C84, C86: N.C.; C0805
C85, C88, C89: 100n; C0603
C87: 4n7; C0805
D18, D19: BAS316; SOD323-R
IC19: LM293D; SOIC127P600X173-8N
IC20: MAX9141ESA; SOIC127P600X173-8N
LED3: WP934MD/LYLID; WP934MD
Q13: BTA26-600; TOP3_TRIAC_NOHOLE
Q14: FMMT493TA; SOT23-BEC
Q15, Q16: 2N7002; SOT103P240X110-3N
Q17: 2N7002; SOT103P240X110-3N; MPN 2N7002-7-F
Q18: PSMN013-60YL; SOT669
Q19: MMBT5551; SOT23-BEC
R83, R90, R92: 330R; R0805
R84, R88, R98, R100: 4K7; R0805
R85: 470R; R0805
R86, R87, R89, R94, R95, R99: 10K; R0805
R91, R101: 1K; R0805
R93: AC01000001007JA100; 0411/15
R96: 100K; R0805
R97: 6R2; R0805
R102, R103: 22K; R0805
ZD4: MMSZ5230BT1G; SOD123

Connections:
!OVP_FAULT: Q17.3 (D); also elsewhere on the board
+5V: LED3.BA (A), LED3.TA (A), R84.2, R98.2; also elsewhere on the board
CC_ACTIVE: Q16.1 (G), R98.1, R100.2; also elsewhere on the board
CC_LED: LED3.BC (C), R92.2
CV_ACTIVE: Q15.1 (G), R84.1, R88.2; also elsewhere on the board
CV_LED: LED3.TC (C), R90.1
D_CC: Q16.3 (D), R92.1
D_CV: Q15.3 (D), R90.2
GND: C84.2, C85.1, C86.1, C88.1, C89.1, D19.C, IC20.4 (GND), Q15.2 (S), Q16.2 (S), Q17.2 (S), R87.1, R89.2, R96.1, R97.1; also elsewhere on the board
I_SERVO: R99.1; also elsewhere on the board
LOOP_CTRL: R94.2; also elsewhere on the board
unnamed: IC20.7 (OUT), Q17.1 (G), R91.2, R101.2
unnamed: Q13.A2, R93.2
unnamed: Q13.G, Q14.C, R85.1
unnamed: Q14.E, R97.2
unnamed: D18.C, D19.A
unnamed: D18.A, Q14.B, R91.1, R96.2
unnamed: R102.2, ZD4.A
unnamed: Q19.B, R102.1, R103.2
unnamed: C87.2, IC20.3 (-IN), R95.2
unnamed: C86.2, C87.1, IC20.2 (+IN), R83.2, R89.1
unnamed: Q18.4 (G), Q19.C, R101.1
unnamed: IC19.1 (OUT), R88.1
unnamed: IC19.7 (OUT), R100.1
unnamed: IC19.2 (-IN), R86.2
unnamed: IC19.6 (-IN), R99.2
unnamed: IC19.3 (+IN), IC19.5 (+IN), R94.1
OVP_EN: IC20.6 (!SHDN), R87.2; also elsewhere on the board
POST_OUTF+: Q13.A1, Q18.MB (D), R85.2, ZD4.C; also elsewhere on the board
PREG_OUT-: Q18.1 (S), Q18.2 (S), Q18.3 (S), Q19.E, R93.1, R103.1; also elsewhere on the board
U_MON: R83.1; also elsewhere on the board
U_SERVO: R86.1; also elsewhere on the board
U_SET_OUT: R95.1; also elsewhere on the board
V+: C84.1, C85.2, C88.2, IC19.8 (V+), IC20.1 (+VCC), IC20.5 (!LE); also elsewhere on the board
V-: C89.2, IC19.4 (V-); also elsewhere on the board

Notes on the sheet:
Licensed under the TAPR Open Hardware License (www.tapr.org/OHL)
Repository: https://github.com/eez-open
More info at http://www.envox.hr/eez
CC/CV mode detection and indication, OVP
Constant Voltage (CV) and Constant Current (CC) mode detection and indication
Over-voltage protection (OVP)
